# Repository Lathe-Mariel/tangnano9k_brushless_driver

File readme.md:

# Overview
 This PCB board was made as a conversion board for Inverter Kit2 that is selling by CQ pub.
 Using this board, you can attach Tang Nano 9K(Sipeed) as an alternative to NUCLEO.
 There's Garber data made by KiCAD.

# BoM
型名 | アイテム（Item）|個数（Quantity）
---|---|---
　| 1608チップコンデンサ1μF | 1
　| 1608チップ抵抗220Ω | 8
　| ダブルピンヘッダ（2x19列） | 2
TVGP01-G73BB with Gray cap | スイッチ | 4
MCP3008-I/P | A-Dコンバータ | 1
2MS1-T1-B4-M2-Q-E | トグルスイッチ | 3
OSL40562-LR | 4桁8セグLED | 1
BP5293-50 | 5VDCDCコンバータ | 1

# FPGA Design
There's a sample project in sample directory.  
The project is files for Gowin EDA which is IDE for Gowin FPGA.
You can download Gowin EDA without any cost.

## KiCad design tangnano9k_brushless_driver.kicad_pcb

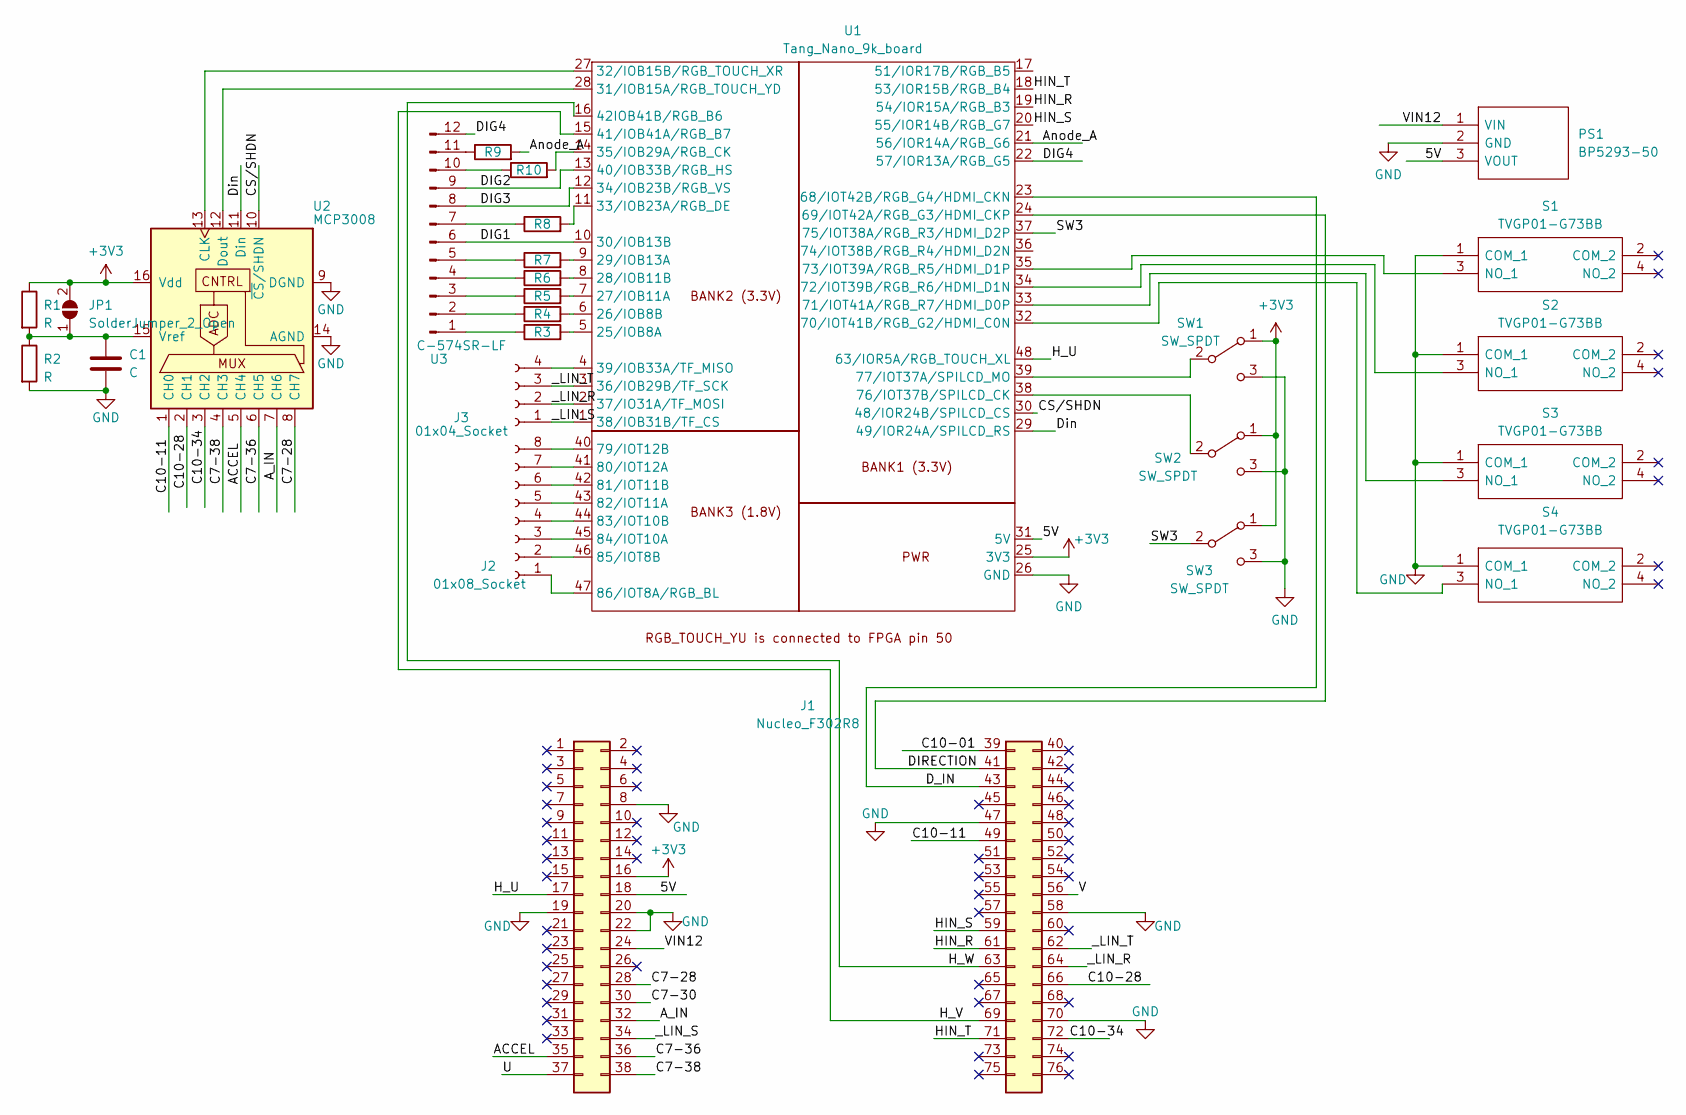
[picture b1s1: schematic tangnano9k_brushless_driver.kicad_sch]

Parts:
C1: C; C_0603_1608Metric_Pad1.08x0.95mm_HandSolder
J1: Nucleo_F302R8; Nucleo
J2: 01x08_Socket; PinSocket_1x08_P2.54mm_Vertical
J3: 01x04_Socket; PinSocket_1x04_P2.54mm_Vertical
JP1: SolderJumper_2_Open; SolderJumper-2_P1.3mm_Open_TrianglePad1.0x1.5mm
PS1: BP5293-50; TO254P570X1700X1780-3P; Manufacturer_Part_Number BP5293-50
R1, R2, R3, R4, R5, R6, R7, R8, R9, R10: R; R_0603_1608Metric_Pad0.98x0.95mm_HandSolder
S1, S2, S3, S4: TVGP01-G73BB; TVGP01G73BB; Manufacturer_Part_Number TVGP01-G73BB
SW1, SW2, SW3: SW_SPDT; PinHeader_1x03_P2.54mm_Vertical
U1: Tang_Nano_9k_board; Tang Nano 9K
U2: MCP3008; DIP-16_W7.62mm
U3: C-574SR-LF

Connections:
+3V3: J1.16, JP1.2 (B), R1.1, SW1.1 (A), SW2.1 (A), SW3.1 (A), U1.25 (3V3), U2.16 (Vdd); also elsewhere on the board
/5V: J1.18, PS1.3 (VOUT), U1.31 (5V); also elsewhere on the board
/ACCEL: J1.35, U2.5 (CH4); also elsewhere on the board
/A_IN: J1.32, U2.7 (CH6); also elsewhere on the board
/Anode_A: R9.2, U1.21 (56/IOR14A/RGB_G6)
/C7-28: J1.28, U2.8 (CH7); also elsewhere on the board
/C7-36: J1.36, U2.6 (CH5); also elsewhere on the board
/C7-38: J1.38, U2.4 (CH3); also elsewhere on the board
/C10-11: J1.49, U2.1 (CH0); also elsewhere on the board
/C10-28: J1.66, U2.2 (CH1); also elsewhere on the board
/C10-34: J1.72, U2.3 (CH2); also elsewhere on the board
/CS/SHDN: U1.30 (48/IOR24B/SPILCD_CS), U2.10 (~CS/SHDN)
/DIG1: U1.10 (30/IOB13B), U3.6 (Cathode_DIG4)
/DIG2: U1.13 (40/IOB33B/RGB_HS), U3.9 (Cathode_DIG2)
/DIG3: U1.12 (34/IOB23B/RGB_VS), U3.8 (Cathode_DIG3)
/DIG4: U1.22 (57/IOR13A/RGB_G5), U3.12 (Cathode_DIG1)
/DIRECTION: J1.41, U1.24 (69/IOT42A/RGB_G3/HDMI_CKP); also elsewhere on the board
/D_IN: J1.43, U1.23 (68/IOT42B/RGB_G4/HDMI_CKN); also elsewhere on the board
/Din: U1.29 (49/IOR24A/SPILCD_RS), U2.11 (Din)
/HIN_R: J1.61, U1.19 (54/IOR15A/RGB_B3); also elsewhere on the board
/HIN_S: J1.59, U1.20 (55/IOR14B/RGB_G7); also elsewhere on the board
/HIN_T: J1.71, U1.18 (53/IOR15B/RGB_B4); also elsewhere on the board
/H_U: J1.17, U1.48 (63/IOR5A/RGB_TOUCH_XL); also elsewhere on the board
/H_V: J1.69, U1.15 (41/IOB41A/RGB_B7); also elsewhere on the board
/H_W: J1.63, U1.16 (42IOB41B/RGB_B6); also elsewhere on the board
/SW3: SW3.2 (B), U1.37 (75/IOT38A/RGB_R3/HDMI_D2P)
/VIN12: J1.24, PS1.1 (VIN); also elsewhere on the board
/_LIN_R: J1.64, J3.2, U1.2 (37/IO31A/TF_MOSI); also elsewhere on the board
/_LIN_S: J1.34, J3.1, U1.1 (38/IOB31B/TF_CS); also elsewhere on the board
/_LIN_T: J1.62, J3.3, U1.3 (36/IOB29B/TF_SCK); also elsewhere on the board
GND: C1.2, J1.8, J1.19, J1.20, J1.22, J1.47, J1.58, J1.70, PS1.2 (GND), R2.2, S1.1 (COM_1), S2.1 (COM_1), S3.1 (COM_1), S4.1 (COM_1), SW1.3 (C), SW2.3 (C), SW3.3 (C), U1.26 (GND), U2.9 (DGND), U2.14 (AGND); also elsewhere on the board
unnamed: J2.1, U1.47 (86/IOT8A/RGB_BL)
unnamed: J2.2, U1.46 (85/IOT8B)
unnamed: J2.3, U1.45 (84/IOT10A)
unnamed: J2.4, U1.44 (83/IOT10B)
unnamed: J2.5, U1.43 (82/IOT11A)
unnamed: J2.6, U1.42 (81/IOT11B)
unnamed: J2.7, U1.41 (80/IOT12A)
unnamed: J2.8, U1.40 (79/IOT12B)
unnamed: J3.4, U1.4 (39/IOB33A/TF_MISO)
unnamed: C1.1, JP1.1 (A), R1.2, R2.1, U2.15 (Vref)
unnamed: S1.3 (NO_1), U1.35 (73/IOT39A/RGB_R5/HDMI_D1P)
unnamed: S2.3 (NO_1), U1.34 (72/IOT39B/RGB_R6/HDMI_D1N)
unnamed: S3.3 (NO_1), U1.33 (71/IOT41A/RGB_R7/HDMI_D0P)
unnamed: S4.3 (NO_1), U1.32 (70/IOT41B/RGB_G2/HDMI_C0N)
unnamed 49: SW1.2 (B), U1.39 (77/IOT37A/SPILCD_MO); also elsewhere on the board
unnamed: SW2.2 (B), U1.38 (76/IOT37B/SPILCD_CK)
unnamed: R3.2, U1.5 (25/IOB8A)
unnamed: R4.2, U1.6 (26/IOB8B)
unnamed: R5.2, U1.7 (27/IOB11A)
unnamed: R6.2, U1.8 (28/IOB11B)
unnamed: R7.2, U1.9 (29/IOB13A)
unnamed: U1.28 (31/IOB15A/RGB_TOUCH_YD), U2.12 (Dout)
unnamed: U1.27 (32/IOB15B/RGB_TOUCH_XR), U2.13 (CLK)
unnamed: R8.2, U1.11 (33/IOB23A/RGB_DE)
unnamed: R10.2, U1.14 (35/IOB29A/RGB_CK)
unnamed: R9.1, U3.11 (Anode_A)
unnamed: R8.1, U3.7 (Anode_B)
unnamed: R6.1, U3.4 (Anode_C)
unnamed: R4.1, U3.2 (Anode_D)
unnamed: R5.1, U3.3 (Anode_DP)
unnamed: R3.1, U3.1 (Anode_E)
unnamed: R10.1, U3.10 (Anode_F)
unnamed: R7.1, U3.5 (Anode_G)

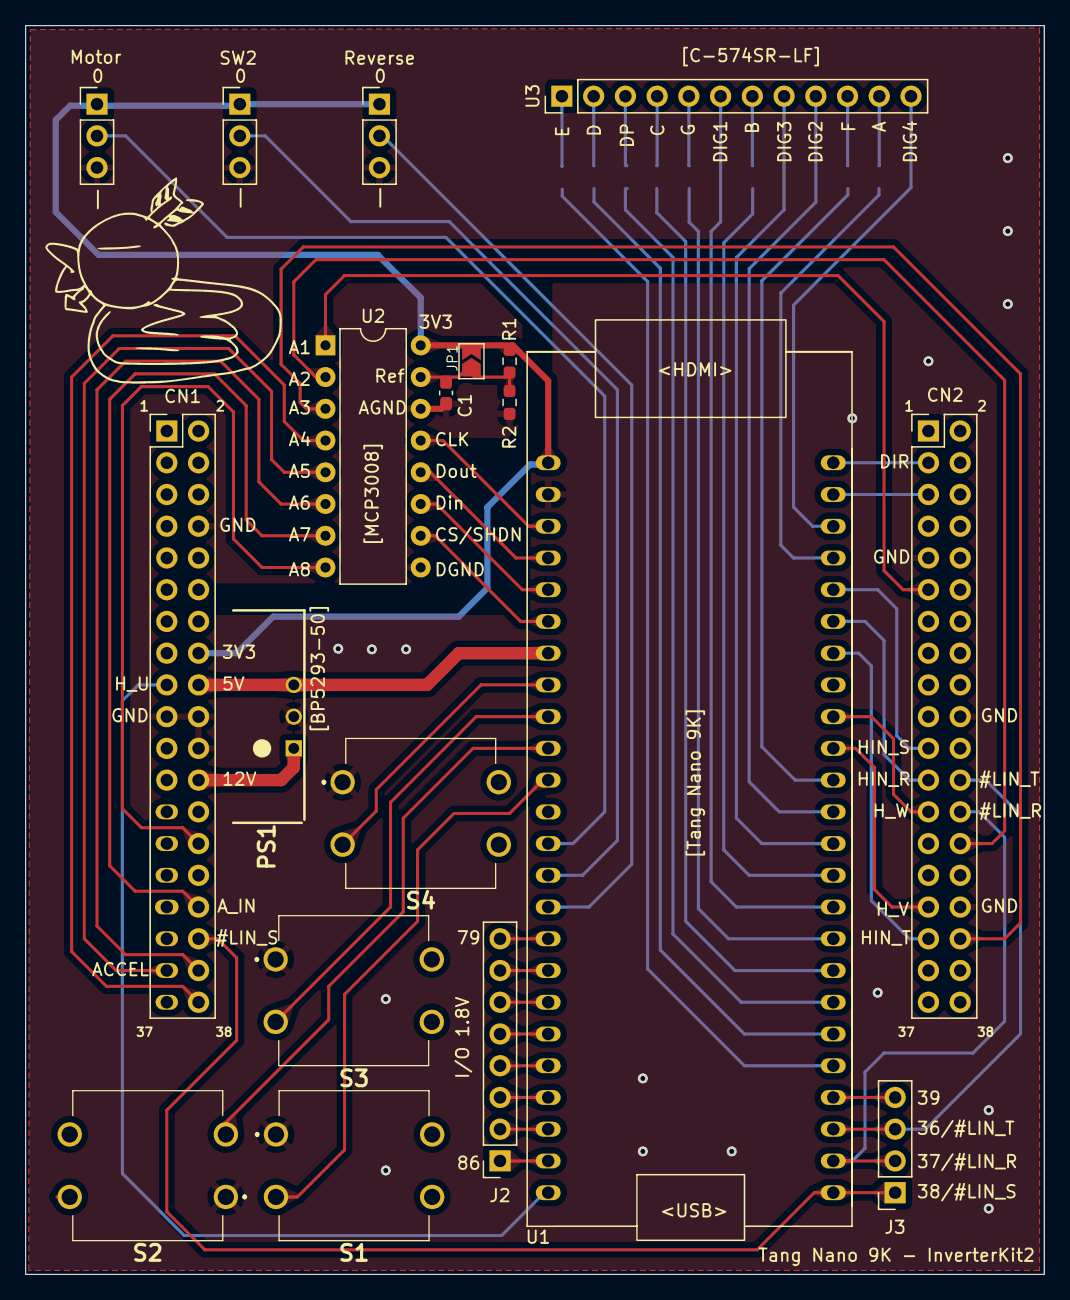
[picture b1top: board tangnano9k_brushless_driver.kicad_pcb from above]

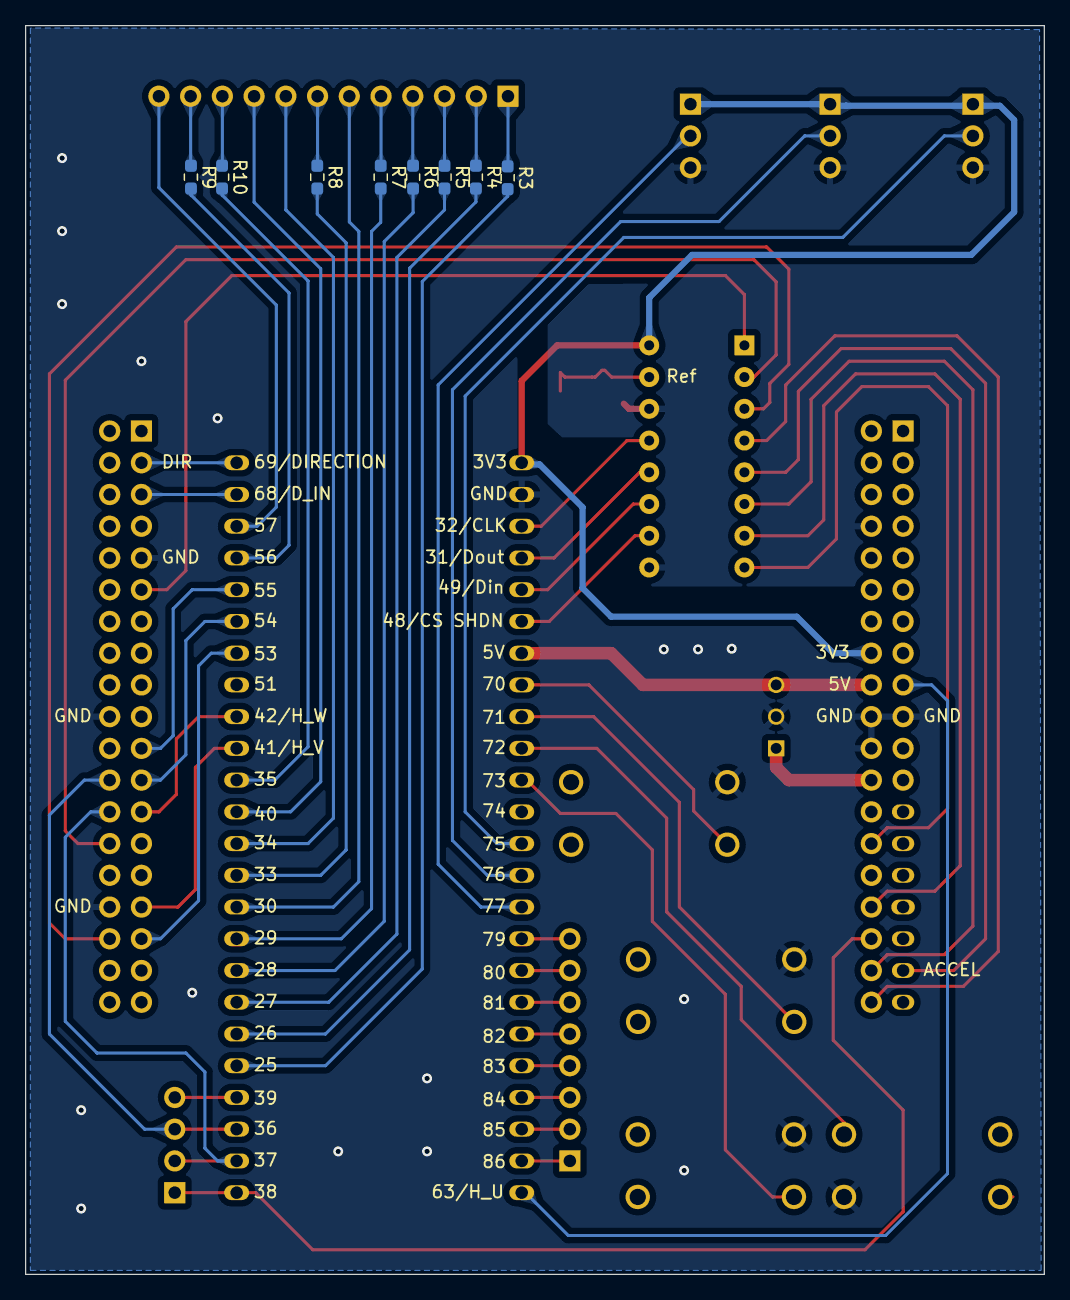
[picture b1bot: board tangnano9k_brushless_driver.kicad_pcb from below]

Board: 2 copper layers, 81.5 x 99.9 mm, 26 parts (8 on the bottom side), 64 nets.

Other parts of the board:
CN1: Nucleo_F302R8; Nucleo
Reverse: SW_SPDT; PinHeader_1x03_P2.54mm_Vertical

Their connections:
+3V3: CN1.16, Reverse.1 (A); also elsewhere on the board
/5V: CN1.18; also elsewhere on the board
/ACCEL: CN1.35; also elsewhere on the board
/A_IN: CN1.32; also elsewhere on the board
/C7-28: CN1.28; also elsewhere on the board
/C7-36: CN1.36; also elsewhere on the board
/C7-38: CN1.38; also elsewhere on the board
/C10-11: CN1.49; also elsewhere on the board
/C10-28: CN1.66; also elsewhere on the board
/C10-34: CN1.72; also elsewhere on the board
/DIRECTION: CN1.41; also elsewhere on the board
/D_IN: CN1.43; also elsewhere on the board
/HIN_R: CN1.61; also elsewhere on the board
/HIN_S: CN1.59; also elsewhere on the board
/HIN_T: CN1.71; also elsewhere on the board
/H_U: CN1.17; also elsewhere on the board
/H_V: CN1.69; also elsewhere on the board
/H_W: CN1.63; also elsewhere on the board
/VIN12: CN1.24; also elsewhere on the board
/_LIN_R: CN1.64; also elsewhere on the board
/_LIN_S: CN1.34; also elsewhere on the board
/_LIN_T: CN1.62; also elsewhere on the board
GND: CN1.8, CN1.19, CN1.20, CN1.22, CN1.47, CN1.58, CN1.70, Reverse.3 (C); also elsewhere on the board
unnamed 49: Reverse.2 (B); also elsewhere on the board

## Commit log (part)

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2023-09-05 0905
2023-09-05 0906
2023-09-06 0907
2023-09-08 0908
2023-09-08 0909
2023-09-16 0916
2023-09-17 0917
2023-09-18 0918
2023-09-19 0919
2023-09-20 0920
2023-09-20 0921
2023-09-21 0922
2023-09-23 0923
2023-09-23 0924
2023-09-25 0925
2023-09-26 0926
2023-09-26 0927
2023-10-05 1005
2023-10-05 1006
2023-10-10 8seg led footprint fix
2023-10-10 1010
2023-10-19 1019
2026-05-14 copilot prompt update
2026-05-14 copilot generated fs
